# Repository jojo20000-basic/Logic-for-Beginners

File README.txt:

Logic-for-Beginners: Modular Logic Kit

An affordable, user-friendly, and open-source system designed to help students explore the world of digital logic through hands-on experimentation.

The Vision

Understanding logic gates is the foundation of computer science, yet learning it from a textbook can be abstract. Our goal is to make logic tangible. This kit allows students to physically connect gates, visualize signal flows in real-time, and build complex circuits from simple building blocks.
🛠 Project Overview

The system consists of uniform, modular Printed Circuit Boards (PCBs) categorized into three functional classes:
1. INPUT Modules

    Function: Generates logical signals (High/Low).

    Control: Dual outputs per board, controlled via tactile slide switches.

    Power: A specialized version includes USB-C Power Delivery to power the entire chain.

    Feedback: Integrated LEDs to show the current state of each output.

2. LOGIC GATES

    Types: AND, OR, NOT, NAND, NOR, XOR.

    Visualization: Every input and output has a dedicated LED, making the signal flow easy to trace.

    Educational Design: Each board is clearly labeled with standardized logic gate symbols.

3. OUTPUT Modules

    Function: Visualizes the final result of a logic chain.

    Display: Dual LED indicators to represent the final states.

    Expansion: Future versions will feature a display for Binary-to-Decimal/Hexadecimal conversion.

Modular Design & Hardware

    Interconnectivity: Boards are designed to be plugged together seamlessly.

    3D-Printed Connectors: To ensure a robust physical connection, we have developed custom-fit 3D-printed mechanical bridges.

    Form Factor: All PCBs share a standardized footprint for easy storage and assembly.

Getting Started

    Conceptual Design: Check out our General Concept File for a deep dive into the architecture.

    PCB Designs: Schematic and layout files are located in the /hardware folder (designed in KiCad).

    Assembly: View the 3D-printing files in /mechanics for the connector bridges.

License

This project is licensed under the MIT License - see the LICENSE file for details.

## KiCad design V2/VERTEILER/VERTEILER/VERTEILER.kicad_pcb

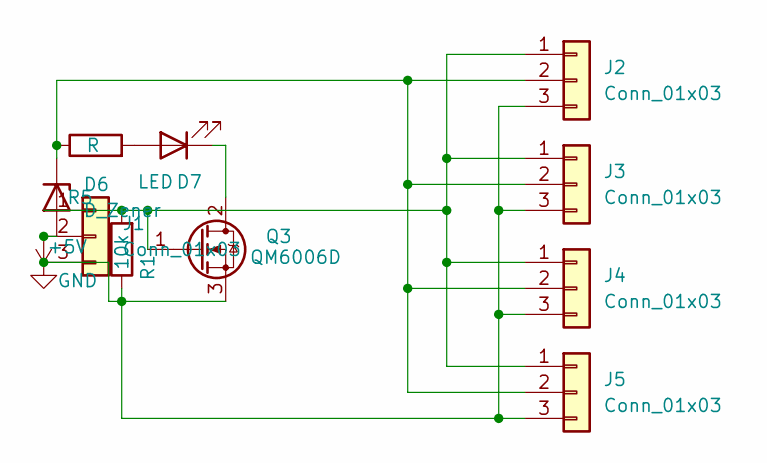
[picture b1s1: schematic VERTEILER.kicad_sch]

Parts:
D6: D_Zener; D_0201_0603Metric
D7: LED; LED_1206_3216Metric
J1: Conn_01x03; PinSocket_1x03_P2.54mm_Horizontal
J2, J3, J4, J5: Conn_01x03; PinHeader_1x03_P2.54mm_Horizontal
Q3: QM6006D; SOT-23
R1: 10k; R_0201_0603Metric
R5: R; R_0201_0603Metric

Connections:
+5V: D6.2 (A), J1.2
GND: J1.3, J2.3, J3.3, J4.3, J5.3, Q3.3 (S), R1.1
unnamed: D6.1 (K), J2.2, J3.2, J4.2, J5.2, R5.1
unnamed: D7.2 (A), R5.2
unnamed: D7.1 (K), Q3.2 (D)
unnamed: J1.1, J2.1, J3.1, J4.1, J5.1, Q3.1 (G), R1.2

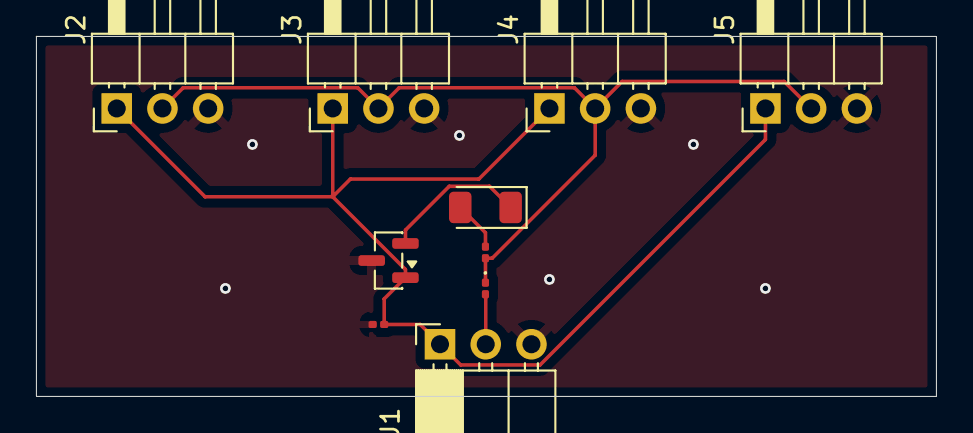
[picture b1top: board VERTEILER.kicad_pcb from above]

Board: 2 copper layers, 50.0 x 20.0 mm, 10 parts (0 on the bottom side), 6 nets.

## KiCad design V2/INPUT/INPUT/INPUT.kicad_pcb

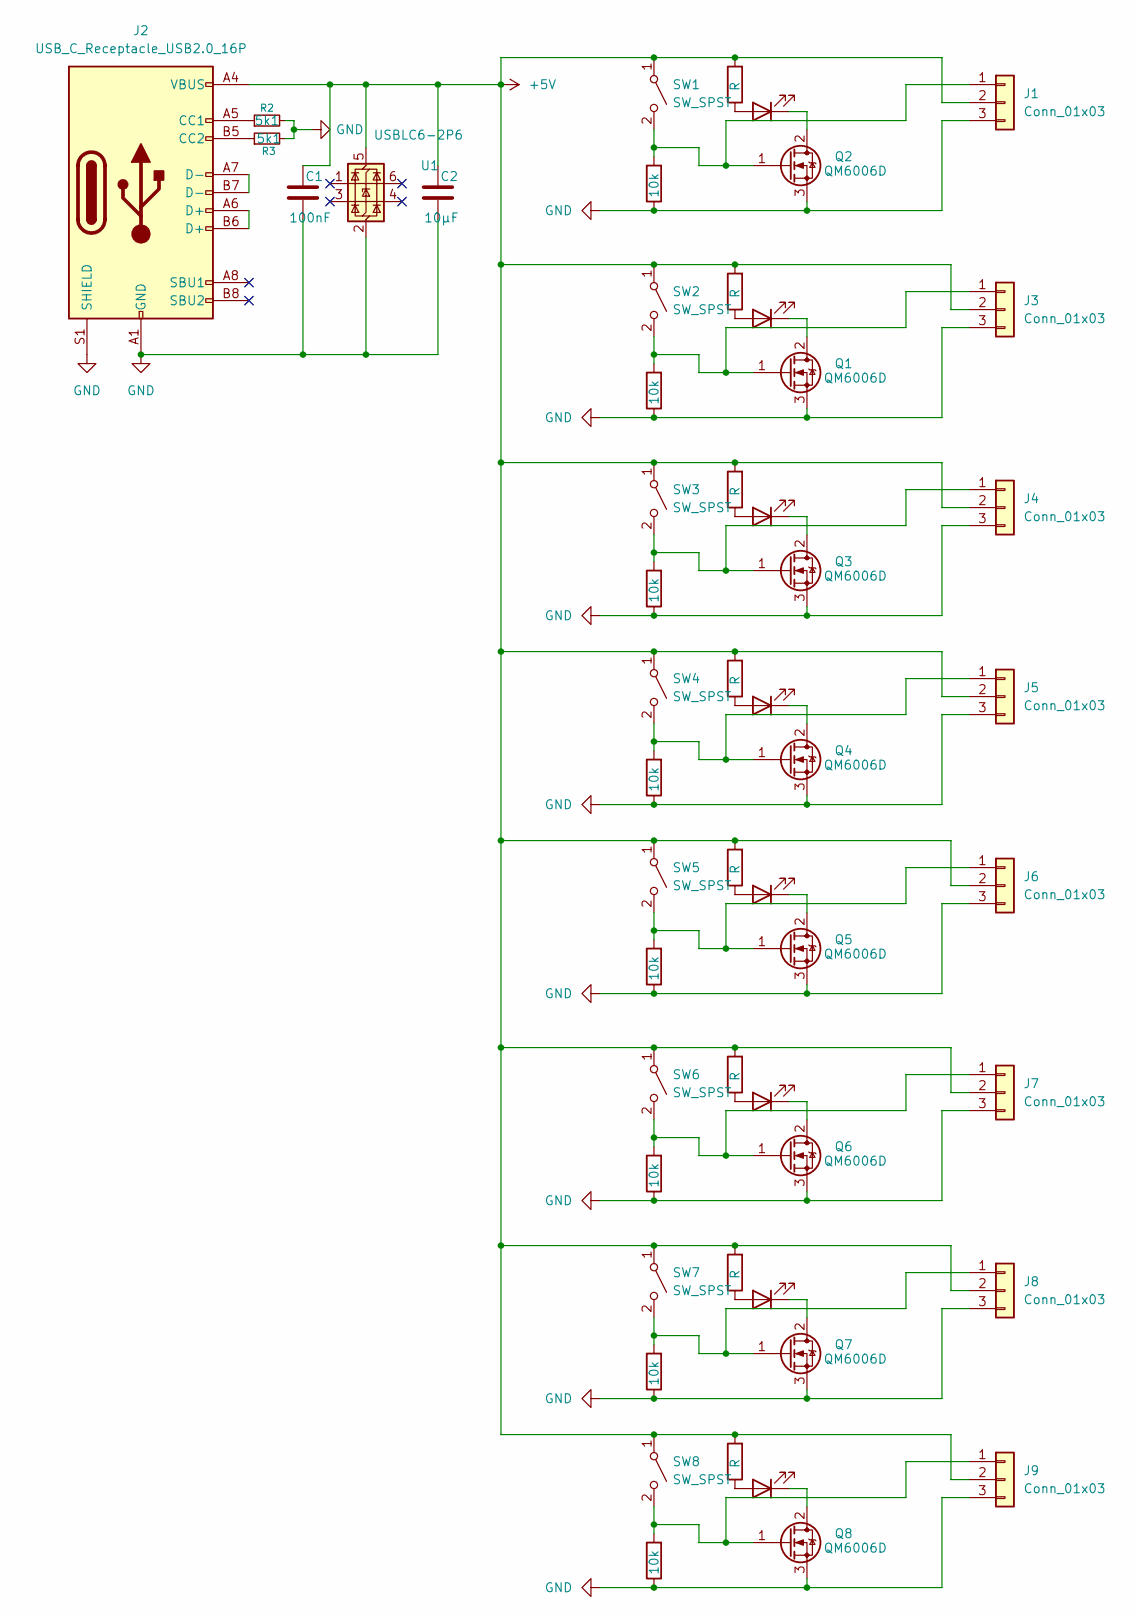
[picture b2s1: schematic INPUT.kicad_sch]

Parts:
C1: 100nF; C_0201_0603Metric
C2: 10µF; C_1206_3216Metric
D1, D2, D3, D4, D5, D6, D7, D8: LED; LED_1206_3216Metric
J1, J3, J4, J5, J6, J7, J8, J9: Conn_01x03; PinSocket_1x03_P2.54mm_Horizontal
J2: USB_C_Receptacle_USB2.0_16P; USB_C_Receptacle_HRO_TYPE-C-31-M-12
Q1, Q2, Q3, Q4, Q5, Q6, Q7, Q8: QM6006D; SOT-23
R1, R5, R7, R9, R11, R13, R15, R17: R; R_0201_0603Metric
R2, R3: 5k1; R_0201_0603Metric
R4, R6, R8, R10, R12, R14, R16, R18: 10k; R_0201_0603Metric
SW1, SW2, SW3, SW4, SW5, SW6, SW7, SW8: SW_SPST; SW_Slide-03_Wuerth-WS-SLTV_10x2.5x6.4_P2.54mm
U1: USBLC6-2P6; SOT-666

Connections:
+5V: C1.1, C2.1, J1.2, J2.A4 (VBUS), J2.A9 (VBUS), J2.B4 (VBUS), J2.B9 (VBUS), J3.2, J4.2, J5.2, J6.2, J7.2, J8.2, J9.2, R1.2, R5.2, R7.2, R9.2, R11.2, R13.2, R15.2, R17.2, SW1.1 (A), SW2.1 (A), SW3.1 (A), SW4.1 (A), SW5.1 (A), SW6.1 (A), SW7.1 (A), SW8.1 (A), U1.5 (VBUS)
GND: C1.2, C2.2, J1.3, J2.A1 (GND), J2.A12 (GND), J2.B1 (GND), J2.B12 (GND), J2.S1 (SHIELD), J3.3, J4.3, J5.3, J6.3, J7.3, J8.3, J9.3, Q1.3 (S), Q2.3 (S), Q3.3 (S), Q4.3 (S), Q5.3 (S), Q6.3 (S), Q7.3 (S), Q8.3 (S), R2.2, R3.2, R4.1, R6.1, R8.1, R10.1, R12.1, R14.1, R16.1, R18.1, U1.2 (GND)
unnamed: D1.2 (A), R1.1
unnamed: D1.1 (K), Q2.2 (D)
unnamed: D2.2 (A), R5.1
unnamed: D2.1 (K), Q1.2 (D)
unnamed: D3.2 (A), R7.1
unnamed: D3.1 (K), Q3.2 (D)
unnamed: D4.2 (A), R9.1
unnamed: D4.1 (K), Q4.2 (D)
unnamed: D5.2 (A), R11.1
unnamed: D5.1 (K), Q5.2 (D)
unnamed: D6.2 (A), R13.1
unnamed: D6.1 (K), Q6.2 (D)
unnamed: D7.2 (A), R15.1
unnamed: D7.1 (K), Q7.2 (D)
unnamed: D8.2 (A), R17.1
unnamed: D8.1 (K), Q8.2 (D)
unnamed: J1.1, Q2.1 (G), R4.2, SW1.2 (B)
unnamed: J2.A5 (CC1), R2.1
unnamed: J2.B5 (CC2), R3.1
unnamed: J2.A6 (D+), J2.B6 (D+)
unnamed: J2.A7 (D-), J2.B7 (D-)
unnamed: J3.1, Q1.1 (G), R6.2, SW2.2 (B)
unnamed: J4.1, Q3.1 (G), R8.2, SW3.2 (B)
unnamed: J5.1, Q4.1 (G), R10.2, SW4.2 (B)
unnamed: J6.1, Q5.1 (G), R12.2, SW5.2 (B)
unnamed: J7.1, Q6.1 (G), R14.2, SW6.2 (B)
unnamed: J8.1, Q7.1 (G), R16.2, SW7.2 (B)
unnamed: J9.1, Q8.1 (G), R18.2, SW8.2 (B)

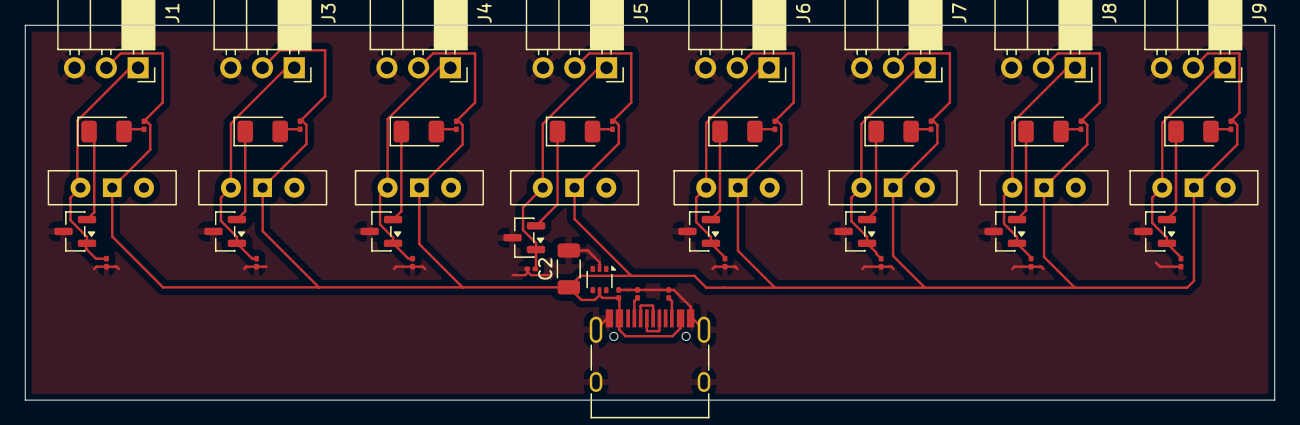
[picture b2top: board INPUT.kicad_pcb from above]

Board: 2 copper layers, 100.0 x 30.0 mm, 54 parts (0 on the bottom side), 30 nets.

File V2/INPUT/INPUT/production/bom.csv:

Designator,Footprint,Quantity,Value,LCSC Part #
C1,1206,1,100nF,
"D1, D2, D3, D4, D5, D6, D7, D8",1206,8,LED,
"J1, J3, J4, J5, J6, J7, J8, J9",PinSocket_1x03_P2.54mm_Horizontal,8,Conn_01x03,
J2,USB_C_Receptacle_HRO_TYPE-C-31-M-12,1,USB_C_Receptacle_USB2.0_16P,
"Q1, Q2, Q3, Q4, Q5, Q6, Q7, Q8",TO-252-2,8,QM6006D,
"R1, R10, R4, R5, R6, R7, R8, R9",1206,8,R,
"R2, R3",1206,2,5k1,
"SW1, SW2, SW3, SW4, SW5, SW6, SW7, SW8",SW_Slide-03_Wuerth-WS-SLTV_10x2.5x6.4_P2.54mm,8,SW_SPST,
U1,SOT-666,1,USBLC6-2P6,

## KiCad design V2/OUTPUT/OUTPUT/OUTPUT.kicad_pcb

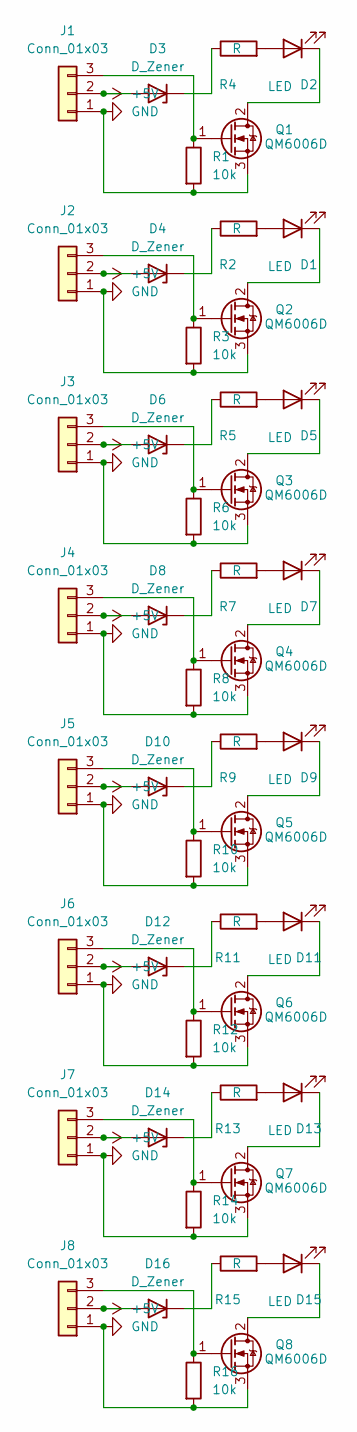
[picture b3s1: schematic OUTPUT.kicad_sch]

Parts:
D1, D2, D5, D7, D9, D11, D13, D15: LED; LED_1206_3216Metric
D3, D4, D6, D8, D10, D12, D14, D16: D_Zener; D_0201_0603Metric
J1, J2, J3, J4, J5, J6, J7, J8: Conn_01x03; PinSocket_1x03_P2.54mm_Horizontal
Q1, Q2, Q3, Q4, Q5, Q6, Q7, Q8: QM6006D; SOT-23
R1, R3, R6, R8, R10, R12, R14, R16: 10k; R_0201_0603Metric
R2, R4, R5, R7, R9, R11, R13, R15: R; R_0201_0603Metric

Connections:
+5V: D3.2 (A), D4.2 (A), D6.2 (A), D8.2 (A), D10.2 (A), D12.2 (A), D14.2 (A), D16.2 (A), J1.2, J2.2, J3.2, J4.2, J5.2, J6.2, J7.2, J8.2
GND: J1.1, J2.1, J3.1, J4.1, J5.1, J6.1, J7.1, J8.1, Q1.3 (S), Q2.3 (S), Q3.3 (S), Q4.3 (S), Q5.3 (S), Q6.3 (S), Q7.3 (S), Q8.3 (S), R1.2, R3.2, R6.2, R8.2, R10.2, R12.2, R14.2, R16.2
unnamed: D1.2 (A), R2.2
unnamed: D1.1 (K), Q2.2 (D)
unnamed: D2.2 (A), R4.2
unnamed: D2.1 (K), Q1.2 (D)
unnamed: D3.1 (K), R4.1
unnamed: D4.1 (K), R2.1
unnamed: D5.2 (A), R5.2
unnamed: D5.1 (K), Q3.2 (D)
unnamed: D6.1 (K), R5.1
unnamed: D7.2 (A), R7.2
unnamed: D7.1 (K), Q4.2 (D)
unnamed: D8.1 (K), R7.1
unnamed: D9.2 (A), R9.2
unnamed: D9.1 (K), Q5.2 (D)
unnamed: D10.1 (K), R9.1
unnamed: D11.2 (A), R11.2
unnamed: D11.1 (K), Q6.2 (D)
unnamed: D12.1 (K), R11.1
unnamed: D13.2 (A), R13.2
unnamed: D13.1 (K), Q7.2 (D)
unnamed: D14.1 (K), R13.1
unnamed: D15.2 (A), R15.2
unnamed: D15.1 (K), Q8.2 (D)
unnamed: D16.1 (K), R15.1
unnamed: J1.3, Q1.1 (G), R1.1
unnamed: J2.3, Q2.1 (G), R3.1
unnamed: J3.3, Q3.1 (G), R6.1
unnamed: J4.3, Q4.1 (G), R8.1
unnamed: J5.3, Q5.1 (G), R10.1
unnamed: J6.3, Q6.1 (G), R12.1
unnamed: J7.3, Q7.1 (G), R14.1
unnamed: J8.3, Q8.1 (G), R16.1

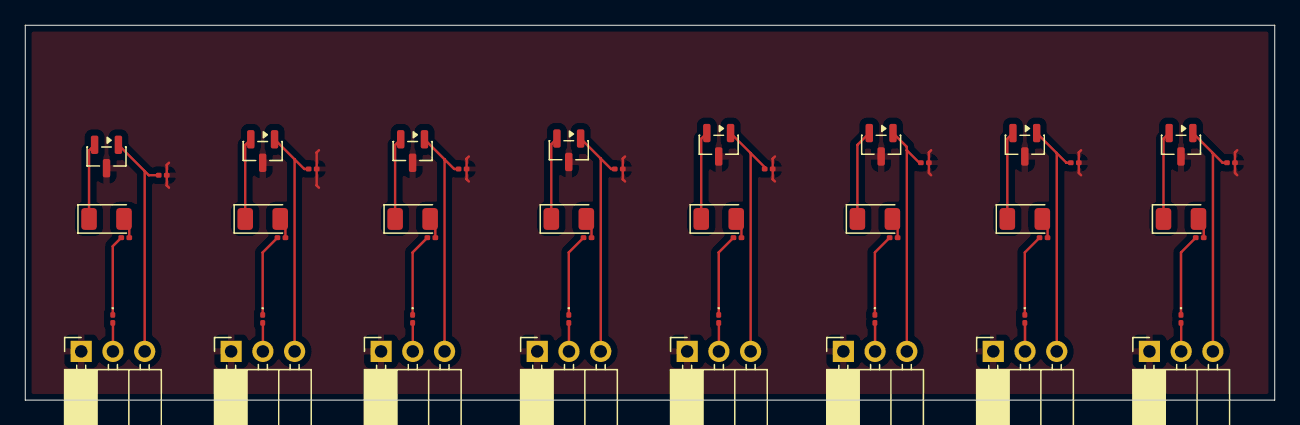
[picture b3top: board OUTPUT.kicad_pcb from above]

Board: 2 copper layers, 100.0 x 30.0 mm, 48 parts (0 on the bottom side), 34 nets.

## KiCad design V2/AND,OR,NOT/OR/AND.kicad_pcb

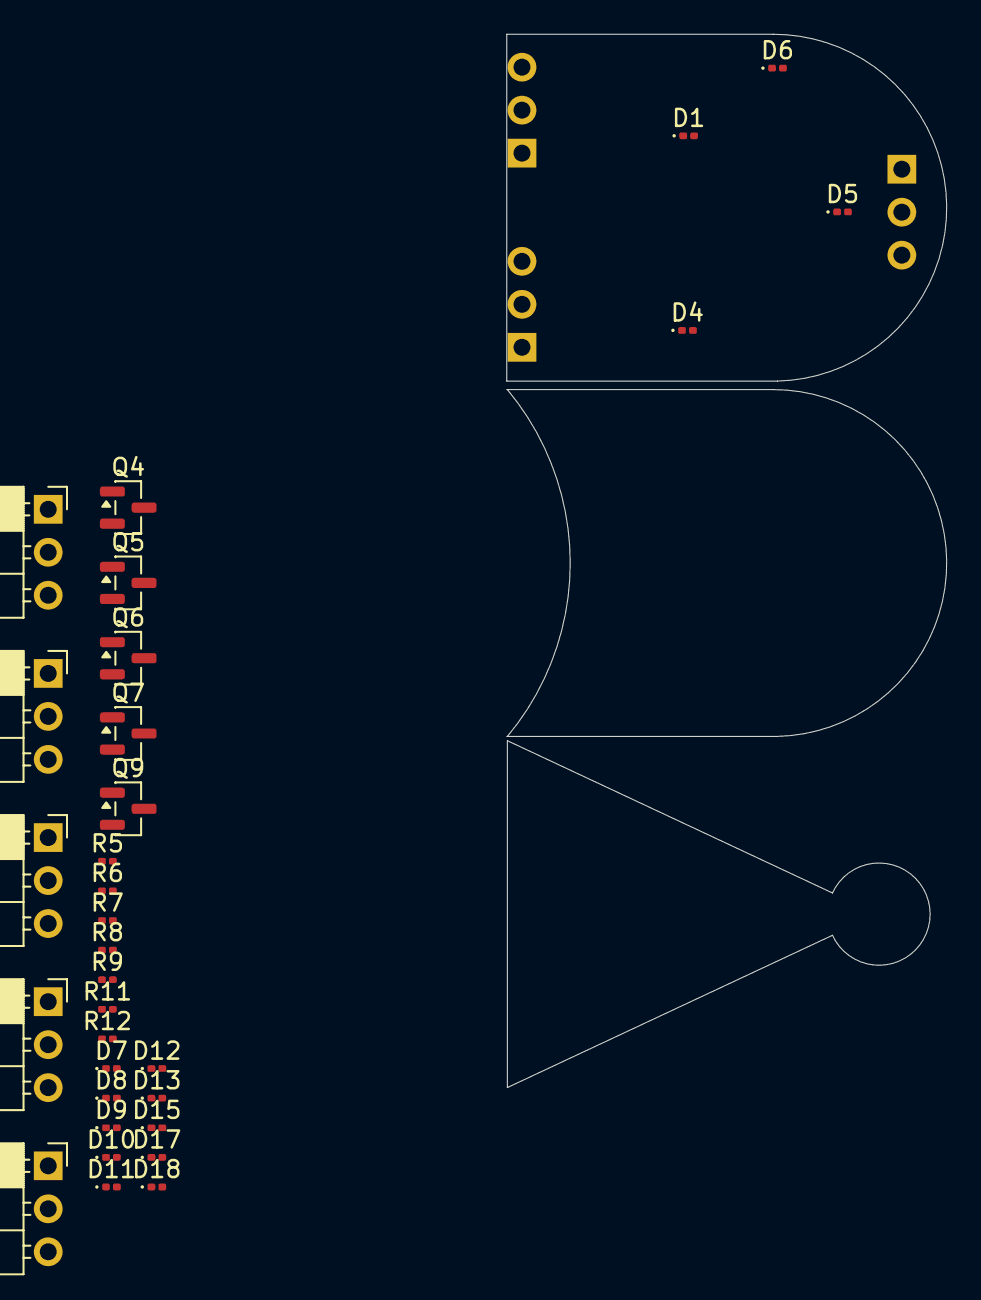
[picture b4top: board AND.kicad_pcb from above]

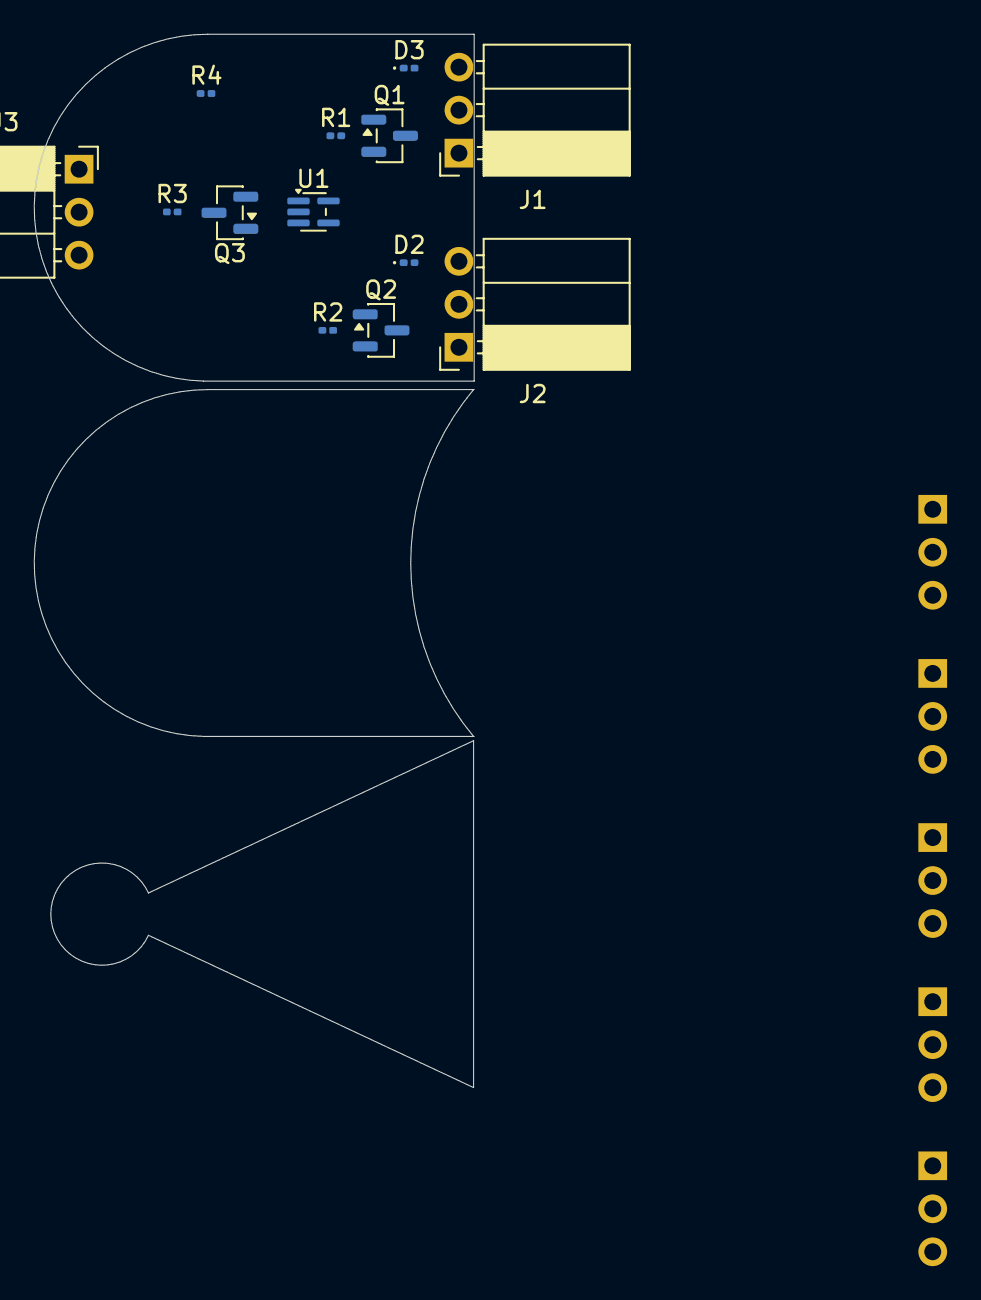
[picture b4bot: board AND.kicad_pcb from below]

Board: 2 copper layers, 26.0 x 62.2 mm, 44 parts (13 on the bottom side), 37 nets, no tracks yet.

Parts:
D1, D4, D5, D6, D9, D10, D11, D12, D15, D17, D18: LED; LED_0201_0603Metric
D2, D3, D7, D8, D13: D; D_0201_0603Metric
J1, J2, J3, J4, J5, J6, J7, J9: Conn_01x03_Socket; PinSocket_1x03_P2.54mm_Horizontal
Q1, Q2, Q3, Q4, Q5, Q6, Q7, Q9: BSS138; SOT-23
R1, R2, R3, R4, R5, R6, R7, R8, R9, R11, R12: R; R_0201_0603Metric
U1: 74LVC1G08; SOT-353_SC-70-5

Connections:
unnamed: D1.2 (A), R1.2
unnamed: D1.1 (K), D2.1 (K), D3.1 (K), D4.1 (K), D5.1 (K), D6.1 (K), J3.3, U1.3 (GND)
unnamed: D2.2 (A), J2.1
unnamed: D3.2 (A), J1.1
unnamed: D4.2 (A), R2.2
unnamed: D5.2 (A), R3.2
unnamed: D6.2 (A), R4.2
unnamed: D7.2 (A), J4.1
unnamed: D8.2 (A), J5.1
unnamed: D9.2 (A), R5.2
unnamed: D10.2 (A), R6.2
unnamed: D7.1 (K), D8.1 (K), D9.1 (K), D10.1 (K), D11.1 (K), D12.1 (K), J6.3
unnamed: D11.2 (A), R7.2
unnamed: D12.2 (A), R8.2
unnamed: D13.2 (A), J7.1
unnamed: D13.1 (K), D15.1 (K), D17.1 (K), D18.1 (K), J7.3, J9.1, J9.3, Q7.2 (S), Q9.2 (S), R11.1
unnamed: D15.2 (A), R9.2
unnamed: D17.2 (A), R11.2
unnamed: D18.2 (A), R12.2
unnamed: J1.2, Q1.1 (G), U1.1
unnamed: J1.3, J2.3, J3.1, Q1.2 (S), Q2.2 (S), Q3.2 (S), R4.1, U1.5 (VCC)
unnamed: J2.2, Q2.1 (G), U1.2
unnamed: J3.2, Q3.1 (G), U1.4
unnamed: J4.2, Q4.1 (G)
unnamed: J4.3, J5.3, J6.1, Q4.2 (S), Q5.2 (S), Q6.2 (S), R7.1
unnamed: J5.2, Q5.1 (G)
unnamed: J6.2, Q6.1 (G)
unnamed: J7.2, Q7.1 (G)
unnamed: J9.2, Q9.1 (G)
unnamed: Q1.3 (D), R1.1
unnamed: Q2.3 (D), R2.1
unnamed: Q3.3 (D), R3.1
unnamed: Q4.3 (D), R5.1
unnamed: Q5.3 (D), R6.1
unnamed: Q6.3 (D), R8.1
unnamed: Q7.3 (D), R9.1
unnamed: Q9.3 (D), R12.1

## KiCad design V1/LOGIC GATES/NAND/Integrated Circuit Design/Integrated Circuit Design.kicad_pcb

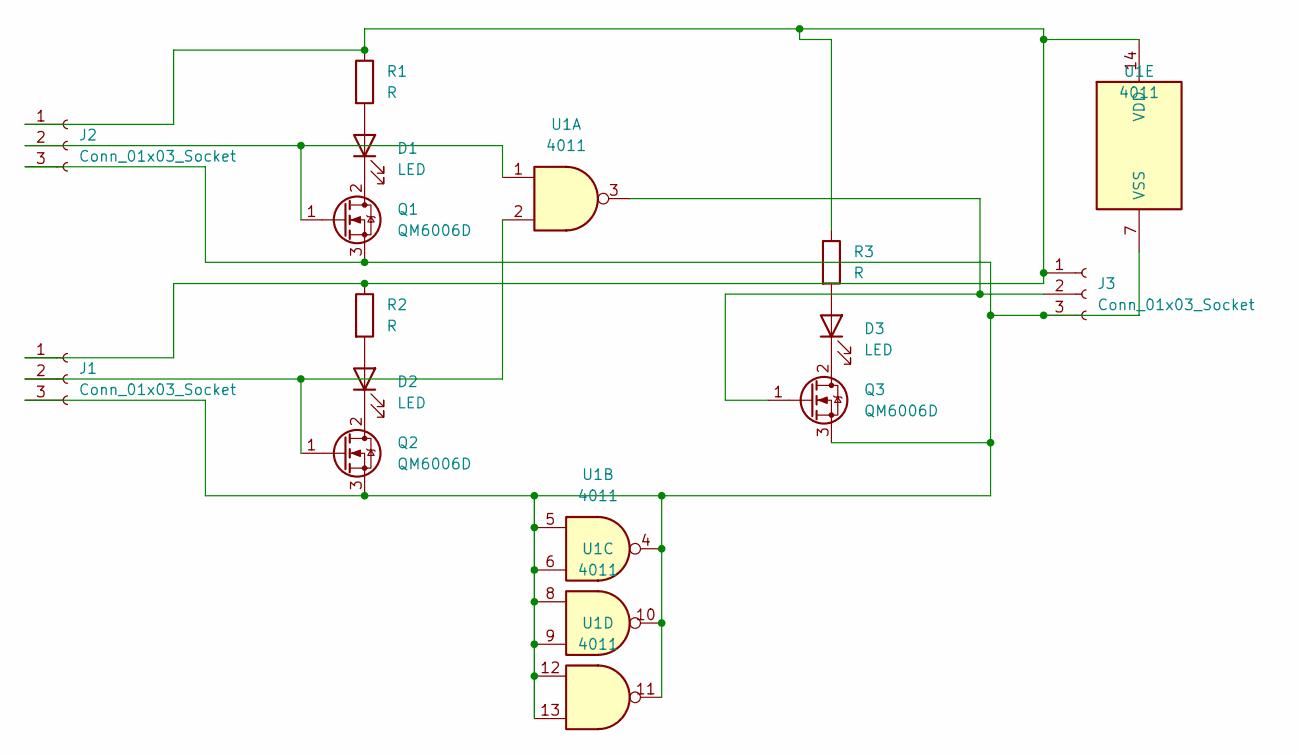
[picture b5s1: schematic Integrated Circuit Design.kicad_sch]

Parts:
D1, D2, D3: LED; LED_1206_3216Metric
J1, J2, J3: Conn_01x03_Socket; PinSocket_1x03_P2.54mm_Horizontal
Q1, Q2, Q3: QM6006D; TO-252-2
R1, R2, R3: R; R_1206_3216Metric
U1: 4011; DIP-14_W7.62mm

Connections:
unnamed: D1.2 (A), R1.2
unnamed: D1.1 (K), Q1.2 (D)
unnamed: D2.2 (A), R2.2
unnamed: D2.1 (K), Q2.2 (D)
unnamed: D3.2 (A), R3.2
unnamed: D3.1 (K), Q3.2 (D)
unnamed: J1.1, J2.1, J3.1, R1.1, R2.1, R3.1, U1.14 (VDD)
unnamed: J1.2, Q2.1 (G), U1.2
unnamed: J1.3, J2.3, J3.3, Q1.3 (S), Q2.3 (S), Q3.3 (S), U1.4, U1.5, U1.6, U1.7 (VSS), U1.8, U1.9, U1.10, U1.11, U1.12, U1.13
unnamed: J2.2, Q1.1 (G), U1.1
unnamed: J3.2, Q3.1 (G), U1.3

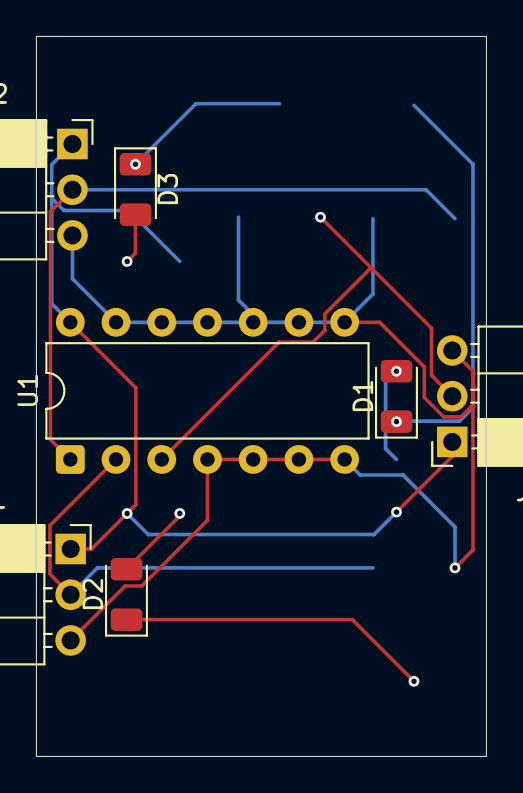
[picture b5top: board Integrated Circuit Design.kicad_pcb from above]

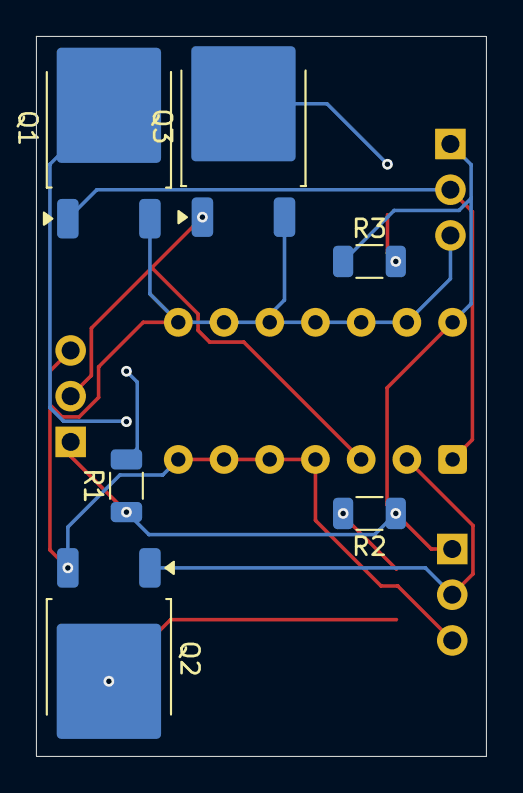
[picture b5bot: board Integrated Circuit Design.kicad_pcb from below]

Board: 2 copper layers, 25.0 x 40.0 mm, 13 parts (6 on the bottom side), 11 nets.

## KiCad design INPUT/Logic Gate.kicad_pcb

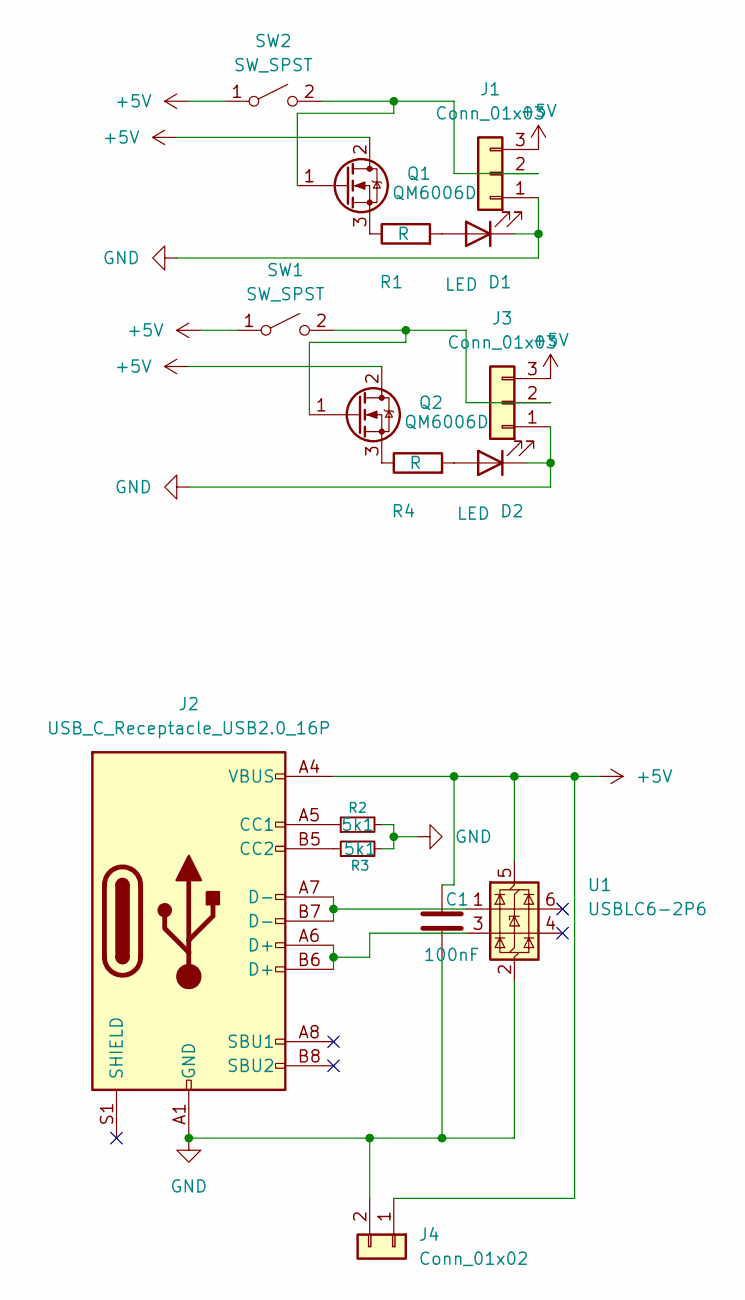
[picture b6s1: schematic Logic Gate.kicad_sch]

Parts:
C1: 100nF; C_1206_3216Metric
D1, D2: LED; LED_1206_3216Metric
J1, J3: Conn_01x03; PinSocket_1x03_P2.54mm_Horizontal
J2: USB_C_Receptacle_USB2.0_16P; USB_C_Receptacle_HRO_TYPE-C-31-M-12
J4: Conn_01x02; PinHeader_1x02_P2.54mm_Horizontal
Q1, Q2: QM6006D; TO-252-2
R1, R4: R; R_1206_3216Metric
R2, R3: 5k1; R_1206_3216Metric
SW1, SW2: SW_SPST; SW_Slide-03_Wuerth-WS-SLTV_10x2.5x6.4_P2.54mm
U1: USBLC6-2P6; SOT-666

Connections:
+5V: C1.1, J1.3, J2.A4 (VBUS), J2.A9 (VBUS), J2.B4 (VBUS), J2.B9 (VBUS), J3.3, J4.1, Q1.2 (D), Q2.2 (D), SW1.1 (A), SW2.1 (A), U1.5 (VBUS)
GND: C1.2, D1.1 (K), D2.1 (K), J1.1, J2.A1 (GND), J2.A12 (GND), J2.B1 (GND), J2.B12 (GND), J3.1, J4.2, R2.2, R3.2, U1.2 (GND)
unnamed: D1.2 (A), R1.2
unnamed: D2.2 (A), R4.2
unnamed: J1.2, Q1.1 (G), SW2.2 (B)
unnamed: J2.A5 (CC1), R2.1
unnamed: J2.B5 (CC2), R3.1
unnamed: J2.A6 (D+), J2.B6 (D+), U1.3 (I/O2)
unnamed: J2.A7 (D-), J2.B7 (D-), U1.1 (I/O1)
unnamed: J3.2, Q2.1 (G), SW1.2 (B)
unnamed: Q1.3 (S), R1.1
unnamed: Q2.3 (S), R4.1

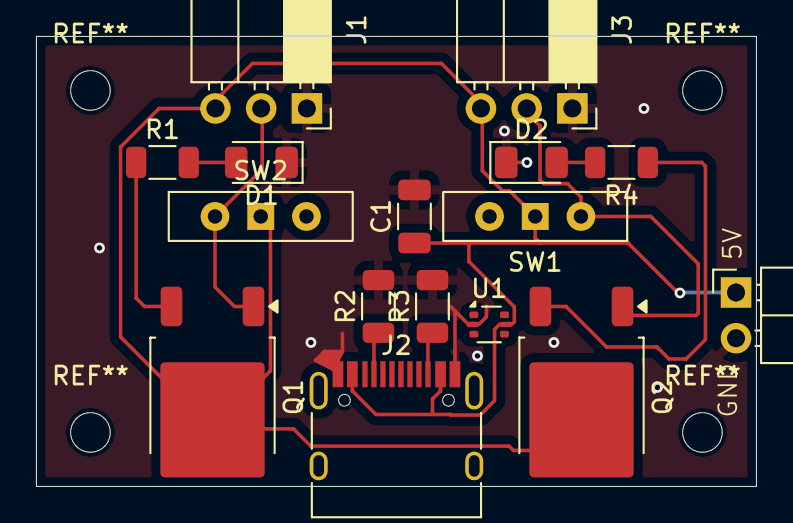
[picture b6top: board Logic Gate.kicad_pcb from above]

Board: 2 copper layers, 40.0 x 25.0 mm, 16 parts (0 on the bottom side), 12 nets.

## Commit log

2025-12-18 Auto-update: 2025-12-18 20:47:05.11
2025-12-18 Auto-update: 2025-12-18 20:49:44.95
2025-12-18 Auto-update: 2025-12-18 20:56:06.77
2025-12-18 Auto-update: 18.12.2025 20:57:15,59
2025-12-18 Rename autoupdate.bat to git-autoupdate.bat
2025-12-18 Auto-update: 18.12.2025 20:57:38,57
2025-12-18 Auto-update: 18.12.2025 20:58:39,73
2025-12-18 Auto-update: 2025-12-18 21:00:20.86
2025-12-18 Auto-update: 2025-12-18 21:03:47.66
2025-12-18 Auto-update: 2025-12-18 21:06:57.11
2025-12-18 Auto-update: 18.12.2025 21:10:38,53
2025-12-18 Auto-update: 2025-12-18 21:35:48.17
2025-12-18 Auto-update: 2025-12-18 21:38:32.31
2025-12-18 Auto-update: 18.12.2025 21:40:25,71
2025-12-18 Auto-update: 2025-12-18 21:48:17.50
2025-12-18 Auto-update: 18.12.2025 21:50:39,79
2025-12-18 Auto-update: 2025-12-18 21:53:44.81
2025-12-18 Create LICENSE
2025-12-18 Create Standardmeasurements
2025-12-18 Create general concept
2025-12-18 Update general concept
2025-12-18 Rename Read Me.txt to README.txt
2025-12-19 Auto-update: 19.12.2025 6:56:17,94
2025-12-19 Auto-update: 19.12.2025 7:18:55,05
2025-12-19 Auto-update: 19.12.2025 7:54:28,40
2025-12-19 Auto-update: 19.12.2025 8:03:36,20
2025-12-19 Auto-update: 20.12.2025 0:17:32,20
2025-12-19 Auto-update: 19.12.2025 15:31:53,15
2025-12-20 Auto-update: 19.12.2025 16:16:57,49
2025-12-20 Auto-update: 19.12.2025 16:17:54,81
2025-12-20 Update Standardmeasurements
2025-12-20 Auto-update: 20.12.2025 1:20:37,71
2025-12-20 Auto-update: 20.12.2025 17:47:44,45
2025-12-20 Auto-update: 20.12.2025 17:48:11,61
2025-12-21 Auto-update: 21.12.2025 12:47:00,10
2025-12-21 Auto-update: 21.12.2025 22:23:26,02
2025-12-21 Auto-update: 21.12.2025 22:24:05,95
2025-12-21 Auto-update: 21.12.2025 13:35:58,67
2025-12-21 Auto-update: 22.12.2025 0:43:45,76
2025-12-21 Auto-update: 22.12.2025 0:44:28,45
2025-12-23 Auto-update: 22.12.2025 16:16:21,18
2025-12-23 Auto-update: 23.12.2025 1:22:13,86
2025-12-23 Auto-update: 23.12.2025 1:31:00,83
2026-01-04 Auto-update: 04.01.2026 11:35:26,02
2026-01-04 Auto-update: 04.01.2026 23:32:30,81
2026-01-04 Auto-update: 04.01.2026 23:34:04,03
2026-01-04 Auto-update: 05.01.2026 0:02:06,37
2026-02-06 Auto-update: 06.02.2026 6:13:30,80
2026-02-06 Auto-update: 06.02.2026 6:14:14,52
2026-02-06 Auto-update: 06.02.2026 6:15:57,27
2026-02-06 Auto-update: 06.02.2026 7:04:32,64
2026-02-15 Auto-update: 15.02.2026 12:08:39,19
2026-02-15 Auto-update: 15.02.2026 14:06:53,52
2026-02-16 Auto-update: 16.02.2026 21:55:36,28
2026-02-16 Auto-update: 17.02.2026 0:08:41,99
2026-02-22 Auto-update: 22.02.2026 23:39:16,59
2026-02-23 Auto-update: 23.02.2026 22:09:21,87
2026-02-23 Auto-update: 24.02.2026 0:09:24,59
2026-02-24 Auto-update: 24.02.2026 16:00:58,58
2026-02-25 Auto-update: 26.02.2026 0:22:57,46
2026-03-27 Auto-update: 28.03.2026 0:16:29,83
2026-03-28 fertige Schematik
    fertige Schematik
2026-03-28 Auto-update: 28.03.2026 23:13:24,41
2026-03-28 Update Zehner
2026-03-28 Auto-update: 28.03.2026 23:45:51,95
2026-03-28 Auto-update: 29.03.2026 0:17:51,75
2026-03-28 Auto-update: 29.03.2026 0:18:01,03
2026-04-15 Auto-update: 15.04.2026 12:38:29,38
2026-04-15 Auto-update: 15.04.2026 12:54:54,95
2026-04-16 Auto-update: 16.04.2026 13:39:12,99
2026-04-16 Auto-update: 16.04.2026 13:58:59,56
2026-04-16 Auto-update: 16.04.2026 14:42:50,23
